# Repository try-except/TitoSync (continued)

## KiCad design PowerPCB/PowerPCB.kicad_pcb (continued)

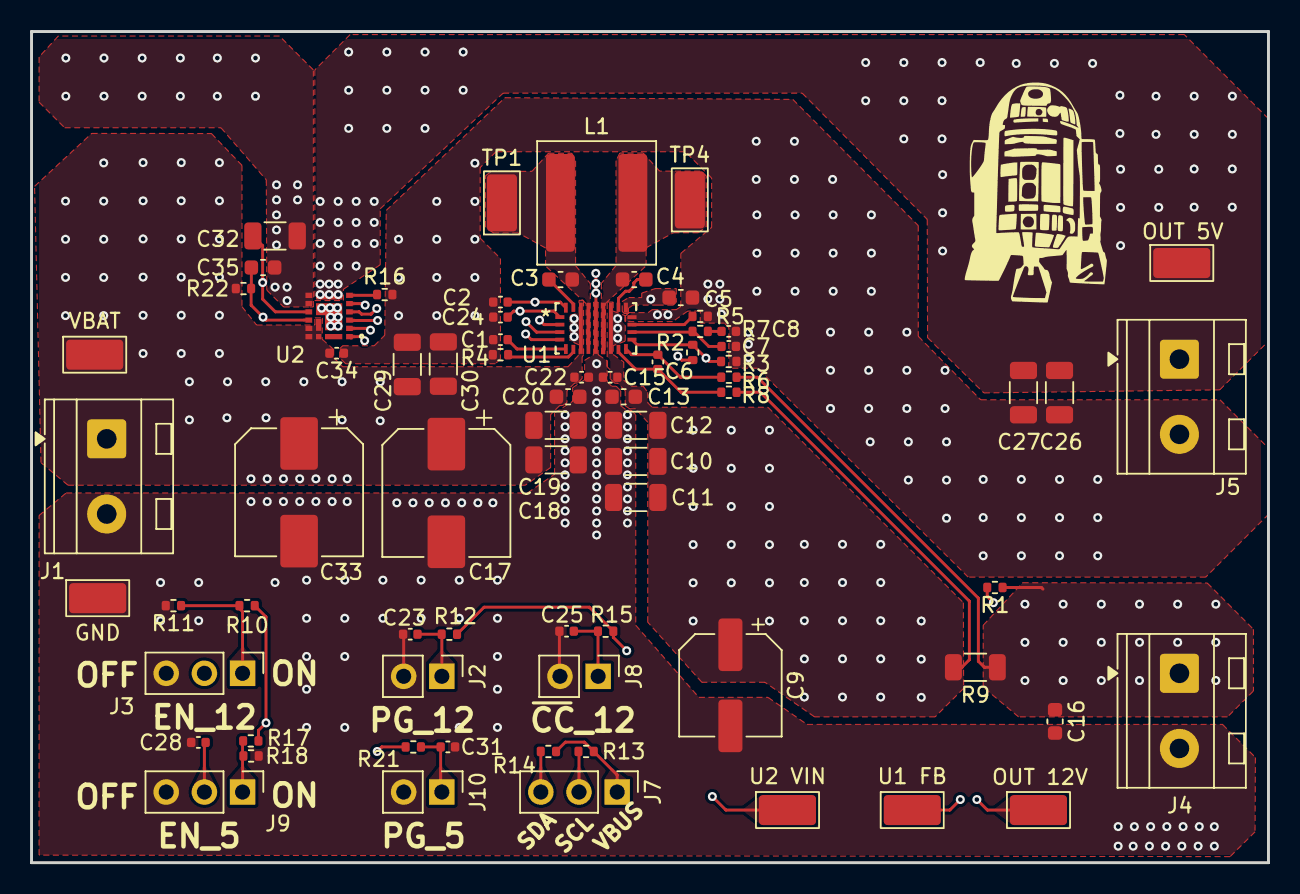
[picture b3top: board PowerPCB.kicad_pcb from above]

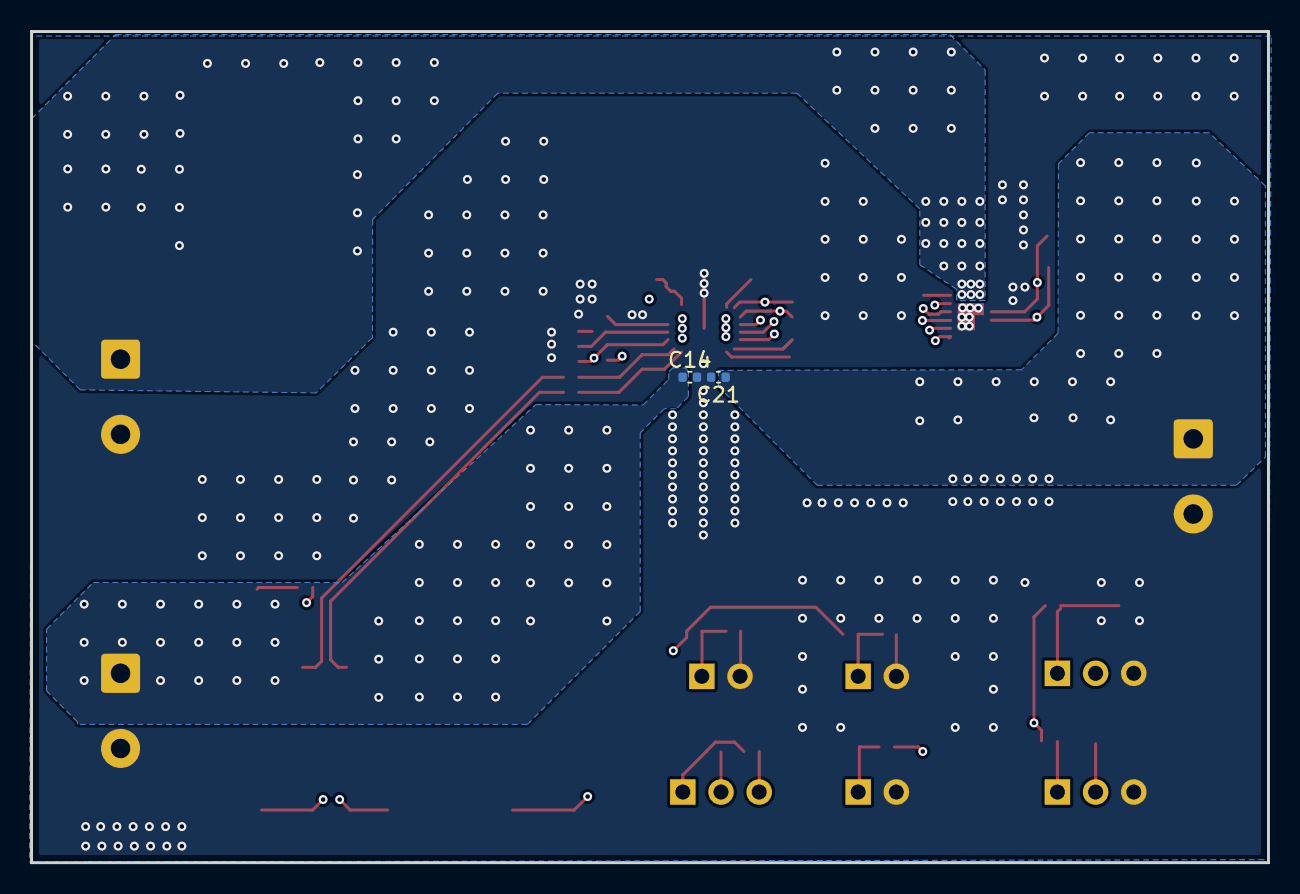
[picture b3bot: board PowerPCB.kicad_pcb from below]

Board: 4 copper layers, 82.3 x 55.3 mm, 75 parts (2 on the bottom side), 31 nets.

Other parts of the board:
GND: TestPoint; TestPoint_Keystone_5019_Miniature
OUT 5V, OUT 12V: TestPoint; TestPoint_Keystone_5019_Miniature
U1 FB, U2 VIN: TestPoint; TestPoint_Keystone_5019_Miniature
VBAT: TestPoint; TestPoint_Keystone_5019_Miniature

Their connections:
GND: GND.1; also elsewhere on the board
unnamed 9: OUT 12V.1; also elsewhere on the board
unnamed 14: U1 FB.1; also elsewhere on the board
unnamed 21: U2 VIN.1; also elsewhere on the board
V_BAT+: VBAT.1; also elsewhere on the board
V_OUT_5+: OUT 5V.1; also elsewhere on the board

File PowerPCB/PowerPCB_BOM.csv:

"Reference","Qty","Value","Footprint","Manufacturer","Description","PartNumber","LCSC"
"C1,C23,C25,C31","4","0.01uF","Capacitor_SMD:C_0402_1005Metric","TDK","CAP, CERM, 0.01 uF, 50 V, +/- 10%, X7R, AEC-Q200 Grade 1, 0402,Unpolarized capacitor","CGA2B3X7R1H103K050BB","C248318"
"C2,C6,C14,C15,C21,C22,C24,C28,C34","9","0.1uF","Capacitor_SMD:C_0402_1005Metric","MuRata,TDK","CAP, CERM, 0.1 uF, 50 V, +/- 10%, X7R, AEC-Q200 Grade 1, 0402,CAP, CERM, 0.1 uF, 50 V, +/- 20%, X7R, 0402","C1005X7R1H104KT000F,GRM155R71H104KE14D"," C77020,C361198"
"C3,C4","2","0.1uF","Capacitor_SMD:C_0603_1608Metric","Murata Electronics North America","0.1μF ±10% 50V Ceramic Capacitor X8L 0603 (1608 Metric)","GCM188L81H104KA57D"," C161181"
"C5","1","4.7uF","Capacitor_SMD:C_0603_1608Metric","MuRata","CAP, CERM, 4.7 μF, 16 V,+/- 10%, X5R, AEC-Q200 Grade 3, 0603","GRT188R61C475KE13D"," C437574"
"C7","1","100pF","Capacitor_SMD:C_0402_1005Metric","TDK","CAP, CERM, 100 pF, 50 V, +/- 5%, C0G/NP0, AEC-Q200 Grade 1, 0402","CGA2B2C0G1H101J050BA"," C2162824"
"C8","1","4700pF","Capacitor_SMD:C_0402_1005Metric","TDK","CAP, CERM, 4700 pF, 50 V, +/- 10%, X7R, AEC-Q200 Grade 1, 0402","C1005X7R1H472KT000F","C694277"
"C9","1","100uF","Capacitor_SMD:CP_Elec_6.3x5.8","Panasonic","CAP, AL, 100 uF, 35 V, AEC-Q200 Grade 2, SMD","EEHZK1V101XP"," C454360"
"C10,C11,C12,C18,C19","5","10uF","Capacitor_SMD:C_1206_3216Metric","TDK","CAP, CERM, 10 μF, 50 V,+/- 10%, X7R, AEC-Q200 Grade 1, 1206","CGA5L1X7R1H106K160AC"," C342827"
"C13,C16,C20,C35","4","1uF","Capacitor_SMD:C_0603_1608Metric","MuRata","CAP, CERM, 1 μF, 50 V,+/- 20%, X5R, AEC-Q200 Grade 3, 0603","GRT188R61H105ME13D"," C3011671"
"C17,C33","2","68uF","Capacitor_SMD:CP_Elec_8x10","Panasonic","CAP, Polymer Hybrid, 68 uF, 50 V, +/- 20%, 30 ohm, 8x10 SMD","EEHZA1H680P"," C542443"
"C26,C27,C29,C30","4","22uF","Capacitor_SMD:C_1206_3216Metric","TDK","Unpolarized capacitor","CGA5L1X7S1A226M160AC "," C2182087"
"C32","1","2.2uF","Capacitor_SMD:C_1206_3216Metric","CCTC","Unpolarized capacitor","TCC1206X7R225M250HT","C5449010"
"J1","1","Battery","TerminalBlock_MetzConnect:TerminalBlock_MetzConnect_Type094_RT03502HBLU_1x02_P5.00mm_Horizontal","DORABO","Generic connector, single row, 01x02, script generated (kicad-library-utils/schlib/autogen/connector/)","DB102-5.0-2P-BU-S","C7498454"
"J2,J8,J10","3","Conn_01x02","Connector_PinHeader_2.54mm:PinHeader_1x02_P2.54mm_Vertical","hanxia","Generic connector, single row, 01x02, script generated (kicad-library-utils/schlib/autogen/connector/)","HX PH254-01-02-Z-L11.5 male header connector","C52016390"
"J3,J7,J9","3","Conn_01x03","Connector_PinHeader_2.54mm:PinHeader_1x03_P2.54mm_Vertical","hanxia","Generic connector, single row, 01x03, script generated (kicad-library-utils/schlib/autogen/connector/)","HX PH254-01-03-Z-L11.5 pcb pin header","C52016391"
"J4","1","12Vout","TerminalBlock_MetzConnect:TerminalBlock_MetzConnect_Type094_RT03502HBLU_1x02_P5.00mm_Horizontal","DORABO","Generic connector, single row, 01x02, script generated (kicad-library-utils/schlib/autogen/connector/)","DB102-5.0-2P-BU-S","C7498454"
"J5","1","5Vout","TerminalBlock_MetzConnect:TerminalBlock_MetzConnect_Type094_RT03502HBLU_1x02_P5.00mm_Horizontal","DORABO","Generic connector, single row, 01x02, script generated (kicad-library-utils/schlib/autogen/connector/)","DB102-5.0-2P-BU-S","C7498454"
"L1","1","4.7uH","Inductor_SMD:L_Coilcraft_XAL7070-XXX","Coilcraft","Inductor, Shielded, Composite, 4.7 uH, 13.6 A, 0.01 ohm, SMD","XAL7070-472MEB"," C3911513"
"R1","1","49.9","Resistor_SMD:R_0402_1005Metric","Vishay-Dale","RES, 49.9, 1%, 0.063 W, AEC-Q200 Grade 0, 0402","CRCW040249R9FKED"," C482189"
"R2,R12,R15","3","102k","Resistor_SMD:R_0402_1005Metric","Vishay-Dale","RES, 102 k, 1%, 0.063 W, AEC-Q200 Grade 0, 0402","CRCW0402102KFKED"," C481920"
"R3","1","11.3k","Resistor_SMD:R_0402_1005Metric","Vishay-Dale","RES, 11.3 k, 1%, 0.063 W, AEC-Q200 Grade 0, 0402","CRCW040211K3FKED"," C481933"
"R4,R17,R21","3","49.9k","Resistor_SMD:R_0402_1005Metric","Vishay-Dale","RES, 49.9 k, 1%, 0.063 W, AEC-Q200 Grade 0, 0402,Resistor, US symbol","CRCW040249K9FKED"," C350874"
"R5","1","150k","Resistor_SMD:R_0402_1005Metric","RESI","RES, 150 k, 1%, 0.063 W, AEC-Q200 Grade 0, 0402","AECR0402F150KK9","C328301 "
"R6,R8","2","10","Resistor_SMD:R_0402_1005Metric","Vishay-Dale","RES, 10.0, 1%, 0.063 W, AEC-Q200 Grade 0, 0402","CRCW040210R0FKED"," C481926"
"R7","1","15k","Resistor_SMD:R_0402_1005Metric","Vishay-Dale","RES, 15.0 k, 1%, 0.063 W, AEC-Q200 Grade 0, 0402","CRCW040215K0FKED"," C191587"
"R9","1","10m","Resistor_SMD:R_1206_3216Metric","Bourns","10 mOhms ±1% 1W Chip Resistor 1206 (3216 Metric) Automotive AEC-Q200, Current Sense, Moisture Resistant Metal Elemen","CRF1206-FZ-R010ELF "," C5629523"
"R10","1","147k","Resistor_SMD:R_0402_1005Metric","FOJAN","RES, 147 k, 1%, 0.063 W, AEC-Q200 Grade 0, 0402","FRC0402F1473TS","C2933073 "
"R11","1","115k","Resistor_SMD:R_0402_1005Metric","Vishay-Dale","RES, 115 k, 1%, 0.063 W, AEC-Q200 Grade 0, 0402","CRCW0402115KFKED"," C2076632"
"R13,R14","2","4.99k","Resistor_SMD:R_0402_1005Metric","Vishay-Dale","Resistor, US symbol","CRCW04024K99FKED"," C482195"
"R16","1","0","Resistor_SMD:R_0402_1005Metric","Vishay-Dale","RES, 0.0, 0.2 W, AEC-Q200 Grade 0, 0402","CRCW04020000Z0EDHP "," C844711"
"R18","1","12.7k","Resistor_SMD:R_0402_1005Metric","Vishay-Dale","Resistor, US symbol","CRCW040212K7FKED "," C481941"
"R22","1","2.7","Resistor_SMD:R_0402_1005Metric","Vishay-Dale","Resistor, US symbol","CRCW040227R0FKED"," C482122"
"TP1,TP2,TP3,TP4,TP7,TP8,TP9,TP11","8","TestPoint","TestPoint:TestPoint_Keystone_5019_Miniature","","test point","5019"," C238131"
"U1","1","TPS551892QWRYQRQ1","Kicad_TitoSync_Footprints:VQFN21_RYQ_TEX","Texas Instruments","","TPS551892QWRYQRQ1"," C42116949"
"U2","1","FS1403-5000-AL","Kicad_TitoSync_Footprints:FS1403_TDK","TDK","","FS1403-5000-AL"," C6253250"

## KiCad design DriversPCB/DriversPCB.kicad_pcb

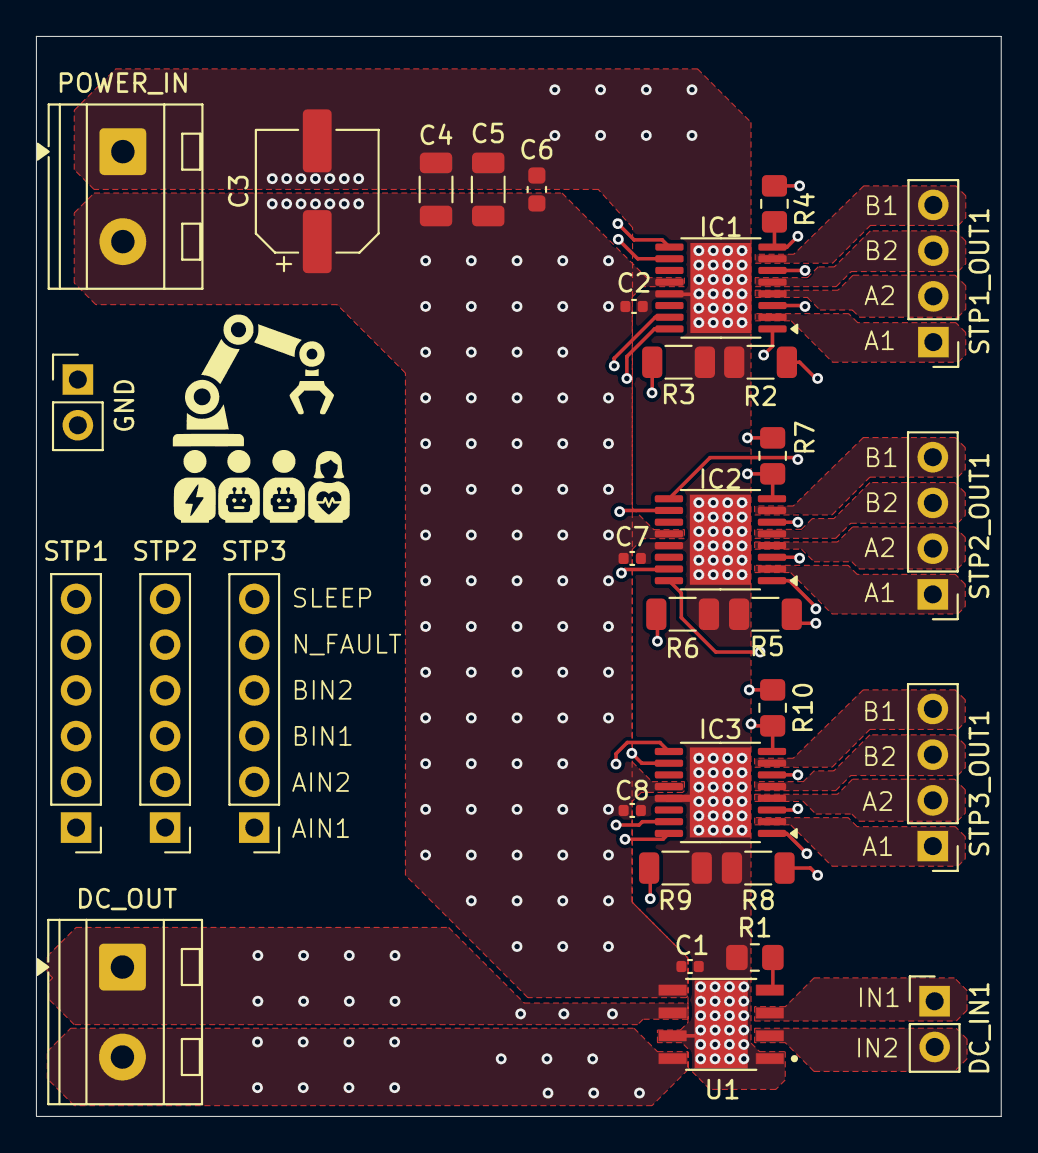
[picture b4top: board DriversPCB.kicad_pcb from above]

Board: 4 copper layers, 53.6 x 60.0 mm, 32 parts (0 on the bottom side), 43 nets.

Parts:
C1, C2, C7, C8: 0.1uF; C_0402_1005Metric
C3: 47uF; CP_Elec_6.3x5.4
C4, C5: 10uF; C_1206_3216Metric
C6: 1uF; C_0603_1608Metric
DC_IN1: DC_CTRL; PinHeader_1x02_P2.54mm_Vertical
GND: Ground Pins; PinHeader_1x02_P2.54mm_Vertical
IC1, IC2, IC3: DRV8411PWPR; HTSSOP-16-1EP_4.4x5mm_P0.65mm_EP3.4x5mm_Mask2.66x2.46mm
J3: DC_OUT; TerminalBlock_MetzConnect_Type094_RT03502HBLU_1x02_P5.00mm_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
POWER_IN: POWER_IN; TerminalBlock_MetzConnect_Type094_RT03502HBLU_1x02_P5.00mm_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
R1: 30k; R_0805_2012Metric_Pad1.20x1.40mm_HandSolder
R2, R3, R5, R6, R8, R9: 100m; R_1206_3216Metric
R4, R7, R10: 1k; R_0805_2012Metric_Pad1.20x1.40mm_HandSolder
STP1: STP1_CTRL; PinHeader_1x06_P2.54mm_Vertical
STP1_OUT1: STP1_OUT; PinHeader_1x04_P2.54mm_Vertical
STP2: STP2_CTRL; PinHeader_1x06_P2.54mm_Vertical
STP2_OUT1: STP2_OUT; PinHeader_1x04_P2.54mm_Vertical
STP3: STP3_CTRL; PinHeader_1x06_P2.54mm_Vertical
STP3_OUT1: STP3_OUT; PinHeader_1x04_P2.54mm_Vertical
U1: DRV8871DDA; VREG_LM5017MR_NOPB

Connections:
AIN1_STP1: IC1.16 (AIN1), STP1.1
AIN1_STP2: IC2.16 (AIN1), STP2.1
AIN1_STP3: IC3.16 (AIN1), STP3.1
AIN2_STP1: IC1.15 (AIN2), STP1.2
AIN2_STP2: IC2.15 (AIN2), STP2.2
AIN2_STP3: IC3.15 (AIN2), STP3.2
AOUT1_STP1: IC1.2 (AOUT1), STP1_OUT1.1
AOUT1_STP2: IC2.2 (AOUT1), STP2_OUT1.1
AOUT1_STP3: IC3.2 (AOUT1), STP3_OUT1.1
AOUT2_STP1: IC1.4 (AOUT2), STP1_OUT1.2
AOUT2_STP2: IC2.4 (AOUT2), STP2_OUT1.2
AOUT2_STP3: IC3.4 (AOUT2), STP3_OUT1.2
BIN1_STP1: IC1.9 (BIN1), STP1.3
BIN1_STP2: IC2.9 (BIN1), STP2.3
BIN1_STP3: IC3.9 (BIN1), STP3.3
BIN2_STP1: IC1.10 (BIN2), STP1.4
BIN2_STP2: IC2.10 (BIN2), STP2.4
BIN2_STP3: IC3.10 (BIN2), STP3.4
BOUT1_STP1: IC1.7 (BOUT1), STP1_OUT1.4
BOUT1_STP2: IC2.7 (BOUT1), STP2_OUT1.4
BOUT1_STP3: IC3.7 (BOUT1), STP3_OUT1.4
BOUT2_STP1: IC1.5 (BOUT2), STP1_OUT1.3
BOUT2_STP2: IC2.5 (BOUT2), STP2_OUT1.3
BOUT2_STP3: IC3.5 (BOUT2), STP3_OUT1.3
FAULT_STP1: IC1.8 (FAULT_N), R4.1, STP1.5
FAULT_STP2: IC2.8 (FAULT_N), R7.1, STP2.5
FAULT_STP3: IC3.8 (FAULT_N), R10.1, STP3.5
GND: C1.1, C2.1, C3.2, C4.1, C5.1, C6.2, C7.1, C8.1, GND.1, GND.2, IC1.13 (GND), IC1.17 (THERMAL_PAD), IC2.13 (GND), IC2.17 (THERMAL_PAD), IC3.13 (GND), IC3.17 (THERMAL_PAD), POWER_IN.1, R1.1, R2.1, R3.2, R5.1, R6.2, R8.1, R9.2, U1.1 (GND), U1.7 (PGND), U1.9
IN1_DC: DC_IN1.1, U1.3 (IN1)
IN2_DC: DC_IN1.2, U1.2 (IN2)
unnamed: IC1.3 (AISEN), R2.2
unnamed: IC1.6 (BISEN), R3.1
unnamed: IC2.3 (AISEN), R5.2
unnamed: IC2.6 (BISEN), R6.1
unnamed: IC3.3 (AISEN), R8.2
unnamed: IC3.6 (BISEN), R9.1
unnamed: R1.2, U1.4 (ILIM)
OUT1_DC: J3.1, U1.6 (OUT1)
OUT2_DC: J3.2, U1.8 (OUT2)
SLEEP_STP1: IC1.1 (SLEEP_N), R4.2, STP1.6
SLEEP_STP2: IC2.1 (SLEEP_N), R7.2, STP2.6
SLEEP_STP3: IC3.1 (SLEEP_N), R10.2, STP3.6
VM: C1.2, C2.2, C3.1, C4.2, C5.2, C6.1, C7.2, C8.2, IC1.12 (VM), IC2.12 (VM), IC3.12 (VM), POWER_IN.2, U1.5 (VM)

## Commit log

2025-09-04 Ignore backup files
2025-09-04 Footprints and Symbols libraries
2025-09-04 Create PowerPCB project
2025-09-04 Add P11F1_TDK footprint
2025-09-09 Ignore backups and buffer files
2025-09-09 Begin PowerPCB schematic
2025-09-09 esquematico mas footprints
2025-09-10 Asignar footprints a símbolo fs1003
2025-09-10 Circuito 12 a 5 faltan valores
2025-09-11 12 V circuit complete
2025-09-11 circuito terminado
2025-09-12 PCB lista falta gerber
2025-09-13 Change FS1003 to FS1403
2025-09-13 Assign footprints
2025-09-14 TPS551892 routed
2025-09-15 'copiaseguridad'
2025-09-15 placa conectada
2025-09-17 Zona cobre...
2025-09-17 ignore fab files
2025-09-17 PCB finished
2025-09-17 Driver PCB complete
2025-09-25 Base ROS
2025-10-07 minor fixes
2025-10-10 Actualiza calibracion, camara y valores; agrega mapa HSV
2025-10-10 Ignorar caches, build, install y log
2025-10-11 codigo listo?
2025-10-15 Placa potencia y ltspice
2025-10-16 Esquemático listo
2025-10-20 minor changes
2025-10-20 PCB routing started
2025-10-20 Routing
2025-10-21 Routing complete
2025-10-21 Correct jumper connections
2025-10-23 control
2025-11-03 PowerPCB v2
2025-11-05 Final PCB revision
2025-11-05 Last PCB revision
2025-11-13 Final PCB
2025-11-20 ignore unimportant files
2025-11-20 rename drivers kicad project
2025-11-20 BOM and Schematic files
2025-11-20 Add gerbers
2025-11-20 Add footprint and symbol library to repo
2025-11-20 clean directory
2025-11-20 upload schematic, BOM and CPL. Update project symbol library
2025-11-20 remove jlcpcb folder
2025-11-20 Add CPL to drivers PCB
2025-11-20 Active load PCB second version
2025-11-20 remove backup files
2025-11-20 clean pull request
2025-11-20 oak_camara
2025-11-20 keyboard control
2025-11-20 Arduino Code
2025-11-24 Ignore pyc files
2025-11-24 Clean pycache, resolve conflict, ignore pyc files
2025-11-24 camara lista
2025-11-30 begin logic board development
2025-12-01 LogicPCB done
2025-12-01 ignore spice outputs
2025-12-01 Minor silkscreen fixes
2025-12-01 clean branch
2025-12-01 remove unused files
2025-12-01 New ROS directory with minimal files
2025-12-02 Add power polarity indicators
2025-12-02 Correct JST header footprint and minor silkscreen changes
2025-12-03 Remove unused ESP32 project files
2025-12-03 remove old ROS folder
